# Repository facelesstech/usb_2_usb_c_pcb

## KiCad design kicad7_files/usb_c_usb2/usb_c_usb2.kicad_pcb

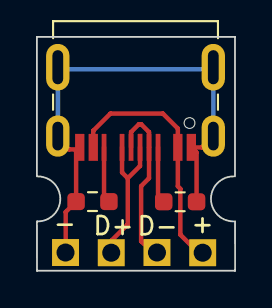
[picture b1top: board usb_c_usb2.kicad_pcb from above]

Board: 2 copper layers, 11.0 x 13.0 mm, 7 parts (0 on the bottom side), 6 nets.

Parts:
+: TestPoint; 1mm_test_point_square
-: TestPoint; 1mm_test_point_square
D+: TestPoint; 1mm_test_point_square
D-: TestPoint; 1mm_test_point_square
P1: USB_C_Plug; USB_C_SMD_USB2
R1, R2: R; R_0603_1608Metric_Pad0.98x0.95mm_HandSolder

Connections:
unnamed: P1.A5 (CC), R1.1
unnamed: D+.1, P1.A6 (D+)
unnamed: D-.1, P1.A7 (D-)
unnamed: -.1, P1.A1 (GND), P1.A12 (GND), P1.S1 (SHIELD), R1.2, R2.2
unnamed: +.1, P1.A4 (VBUS), P1.A9 (VBUS)
unnamed: P1.B5 (VCONN), R2.1

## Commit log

2024-01-14 added kicad 7 files
